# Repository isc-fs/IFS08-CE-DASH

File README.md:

# IFS08 - CE_DASH

Embedded firmware for the **Dashboard (DASH)** of the IFS08, developed on STM32.

---

## Getting started

1. Create a GitHub account if you don't have one yet.
2. Download and install [GitHub Desktop](https://desktop.github.com/) (beginner) or [Git CLI](https://git-scm.com/book/en/v2/Getting-Started-Installing-Git) (advanced).

   - If this is your first time using GitHub Desktop, make sure to read the [User Manual](https://help.github.com/desktop/guides/).
   - If this is your first time using Git, start with a tutorial. There are many available online:
     - [Git Tutorial](https://git-scm.com/docs/gittutorial)
     - [Atlassian Git Tutorial](https://www.atlassian.com/git/tutorials/)
   - Keep a copy of [GitHub's Git Cheat Sheet](https://services.github.com/kit/downloads/github-git-cheat-sheet.pdf) handy as a reference.

3. Clone this repository to your machine:
   - SSH: `git@github.com:isc-fs/IFS08-CE-DASH.git`
   - HTTPS: `https://github.com/isc-fs/IFS08-CE-DASH.git`

---

## How we work with this repository

### Main branches

The repository has two permanent branches:

**`main`** is the production branch. It contains only validated code that can be flashed onto the car. Never work directly on it.

**`dev`** is the development branch. It is the integration point where everyone's work comes together. Never work directly on it either — all changes arrive through a feature branch.

```
main  ──────────────────●──────────────────────●──▶  (validated releases only)
                        ↑                      ↑
dev   ──────●───●───●───●───●───●───●───●───●──●──▶  (continuous integration)
            ↑   ↑       ↑   ↑   ↑       ↑   ↑
          feat/1 fix/1 feat/2 fix/2   feat/3 fix/3
```

### Feature branches

All work — whether a new feature or a bug fix — is done on a **feature branch** created from `dev`. When the work is ready, a Pull Request is opened toward `dev`, reviewed, merged, and the branch is deleted.

There are two branch types, each with its own independent numeric counter. Every branch name carries a short kebab-case title after the number so its purpose is visible at a glance:

```
feat/<n>-<short-title>   →  new functionality  (feat/1-frame-layout, feat/2-isotp, ...)
fix/<n>-<short-title>    →  bug fix            (fix/1-wrp-race,      fix/2-crc-pad,  ...)
```

The short title should be 2–4 lowercase words joined by dashes. The `feat` and `fix` counters are independent: `feat/2-…` and `fix/2-…` can exist at the same time with no conflict.

### Tracking branch history

Feature branches are deleted after merging to keep the repository clean. The history of each branch is preserved in **GitHub Issues**.

Every branch has one associated issue. The issue carries a **label** (`feat` or `fix`) and its title includes the full branch name, for example: `[feat/3-can-broadcast] Add CAN broadcast for mission state`. When the branch is merged and deleted, the issue is closed — becoming a permanent record of all the work done.

To see which branches are currently active: filter issues by label and status `open`.
To browse the full history: filter by label and status `closed`.
The number for the next branch of each type is the last closed issue of that type plus one.

> Example: if the last closed issue with label `feat` is `[feat/4-…] ...`, the next feature branch will be `feat/5-<your-title>`.

---

## Automation

The repository includes a GitHub Actions workflow that manages tracking issues automatically. No setup is required — it works for every developer as soon as they create a branch.

### Automatic issue creation

When a `feat/*` or `fix/*` branch is pushed to GitHub, the workflow automatically opens an issue with:

- A title that mirrors the branch name — `[feat/N-short-title]` or `[fix/N-short-title]`
- The correct label (`feat` or `fix`)
- A template with sections for describing the work and adding notes
- The name of the developer who created the branch

### Wrong number warning

If the branch number is not the next expected one (either too low or too high), the issue will display a warning indicating the correct number and asking the developer to delete and recreate the branch with the right name.

### Auto-fill description from first commit

When the developer makes their first commit and pushes it, the workflow automatically updates the *"What does this branch do?"* section of the issue with that commit message.

- If the developer manually edits the issue before pushing their first commit, the workflow will not overwrite the description.
- The description is only updated once — subsequent commits do not modify the issue.

---

## Step-by-step workflow

### 1. Create the branch

```bash
# Make sure you are on an up-to-date dev
git checkout dev
git pull origin dev

# Create your branch using the next available number for its type
# (last closed issue of that type + 1) plus a short kebab-case title
git checkout -b feat/5-frame-layout    # or fix/3-wrp-race, etc.
```

> To find the right number: go to **Issues → filter by label `feat` or `fix` → sort by newest** and read the last number.

### 2. Push the branch

```bash
git push origin feat/5-frame-layout
```

The tracking issue will be opened automatically on GitHub within seconds.

### 3. Work and commit

```bash
# Make your changes and commit with a clear, descriptive message
git add .
git commit -m "short description of what this commit does"

# Push the changes
git push origin feat/5-frame-layout
```

The message of your **first commit** will be used to automatically fill in the issue description.

### 4. Open a Pull Request

When the work is ready, open a Pull Request on GitHub from your branch toward `dev`. In the PR description write `Closes #<issue-number>` so the issue closes automatically when the PR is merged.

Before requesting a review, check that:
- The code compiles with no errors or warnings
- You have tested the change on the bench if applicable
- The PR targets `dev`, not `main`

### 5. Review and merge

Another team member will review the PR. Once approved, it is merged into `dev` and the branch is deleted. The issue will be closed as a permanent record.

### 6. Merging into main

When `dev` holds a set of validated changes that are ready for the car, a responsible team member opens a Pull Request from `dev` into `main`. This only happens after full firmware validation (HIL/bench).

---

*ISC Racing Team — IFS08 Car Electronics*

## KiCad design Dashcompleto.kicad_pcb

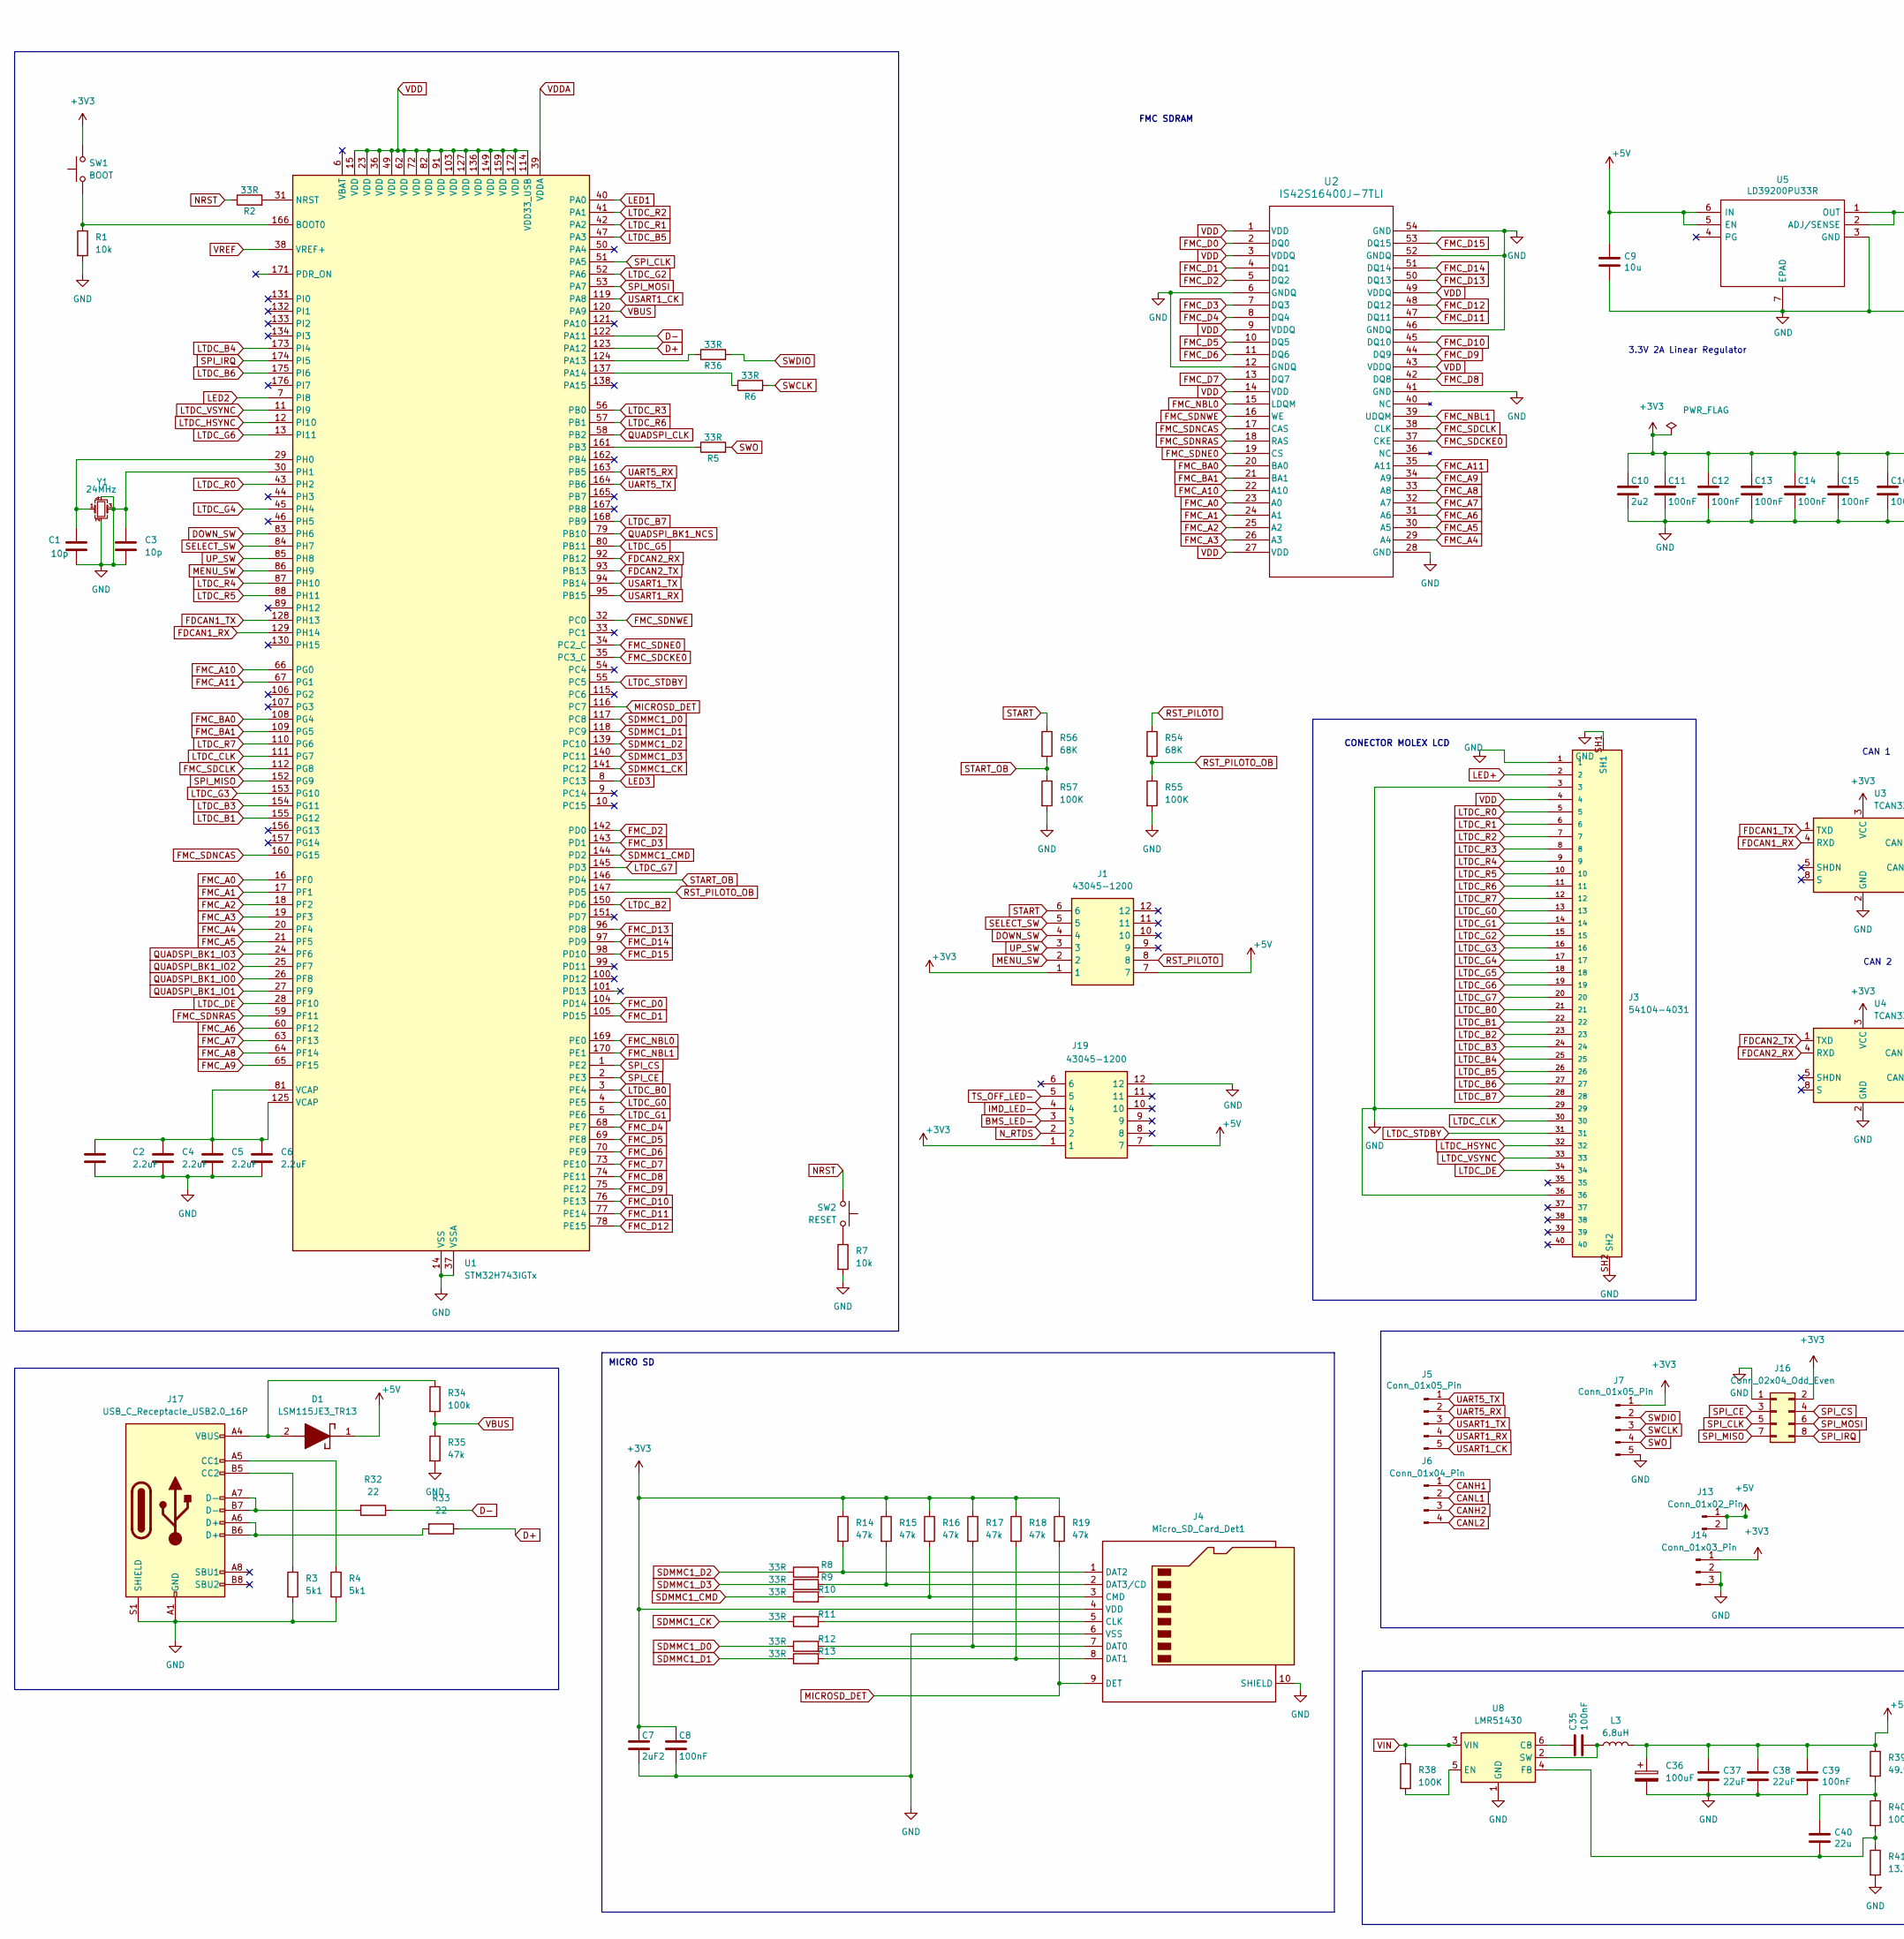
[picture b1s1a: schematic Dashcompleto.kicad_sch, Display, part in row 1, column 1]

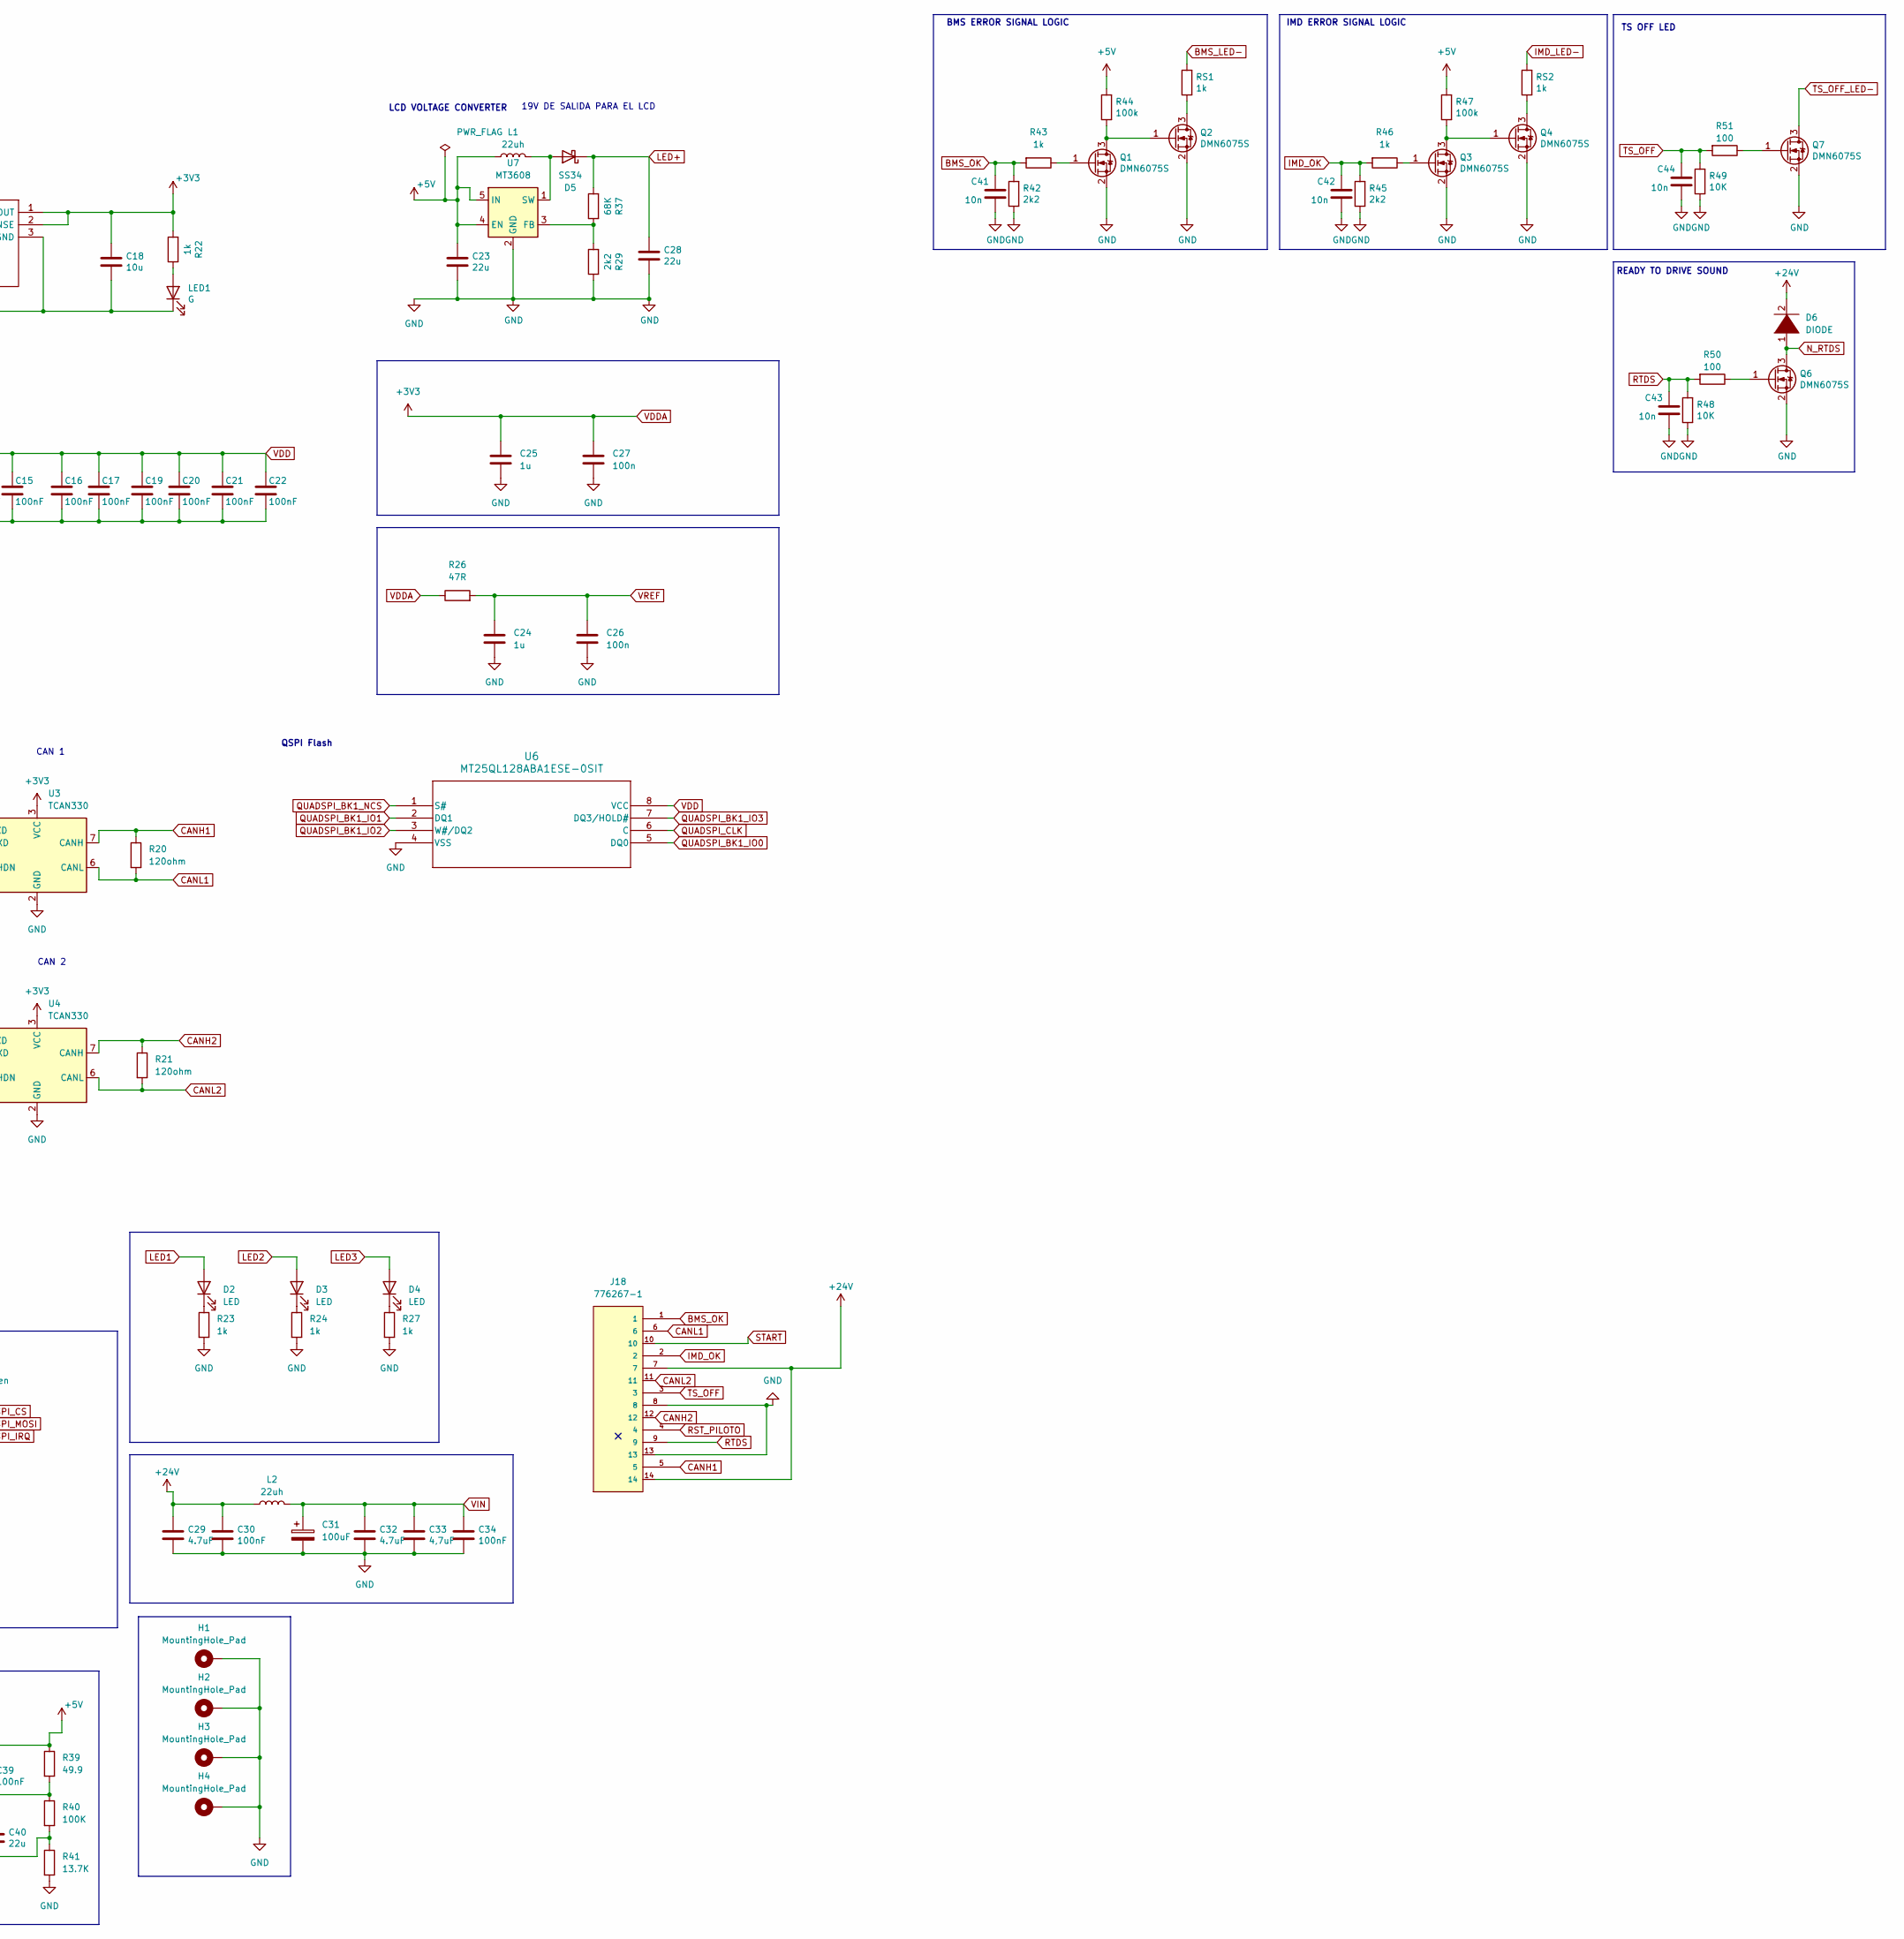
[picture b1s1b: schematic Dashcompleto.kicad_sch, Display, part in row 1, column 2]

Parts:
C1, C3: 10p; C_0805_2012Metric_Pad1.18x1.45mm_HandSolder
C2, C4, C5, C6: 2.2uF; C_0805_2012Metric_Pad1.18x1.45mm_HandSolder
C7: 2uF2; C_0805_2012Metric_Pad1.18x1.45mm_HandSolder
C8, C11, C12, C13, C14, C15, C16, C17, C19, C20, C21, C22, C30, C34, C35, C39: 100nF; C_0805_2012Metric_Pad1.18x1.45mm_HandSolder
C9, C18: 10u; C_0805_2012Metric_Pad1.18x1.45mm_HandSolder
C10: 2u2; C_0805_2012Metric_Pad1.18x1.45mm_HandSolder
C23, C28, C40: 22u; C_0805_2012Metric_Pad1.18x1.45mm_HandSolder
C24, C25: 1u; C_0805_2012Metric_Pad1.18x1.45mm_HandSolder
C26, C27: 100n; C_0805_2012Metric_Pad1.18x1.45mm_HandSolder
C29, C32: 4.7uF; C_0805_2012Metric_Pad1.18x1.45mm_HandSolder
C31, C36: 100uF; C_0805_2012Metric_Pad1.18x1.45mm_HandSolder
C33: 4,7uF; C_0805_2012Metric_Pad1.18x1.45mm_HandSolder
C37, C38: 22uF; C_0805_2012Metric_Pad1.18x1.45mm_HandSolder
C41, C42, C43, C44: 10n; C_1210_3225Metric
D1: LSM115JE3_TR13; DIOM5436X330N; Mouser Part Number 494-LSM115JE3/TR13
D2, D3, D4: LED; LED_0805_2012Metric_Pad1.15x1.40mm_HandSolder
D5: SS34; D_SMA
D6: DIODE; D_0805_2012Metric_Pad1.15x1.40mm_HandSolder
H1, H2, H3, H4: MountingHole_Pad; MountingHole_3.2mm_M3_ISO14580_Pad_TopBottom
J1, J19: 43045-1200; Molex_Micro-Fit_3.0_43045-1200_2x06_P3.00mm_Horizontal; Manufacturer_Part_Number 43045-1200
J3: 54104-4031; MOLEX_54104-4031; PARTREV A
J4: Micro_SD_Card_Det1; microSD_HC_Molex_104031-0811
J5, J7: Conn_01x05_Pin; PinHeader_1x05_P2.54mm_Vertical
J6: Conn_01x04_Pin; PinHeader_1x04_P2.54mm_Vertical
J13: Conn_01x02_Pin; PinHeader_1x02_P2.54mm_Vertical
J14: Conn_01x03_Pin; PinHeader_1x03_P2.54mm_Vertical
J16: Conn_02x04_Odd_Even; PinHeader_2x04_P2.54mm_Vertical
J17: USB_C_Receptacle_USB2.0_16P; USB_C_Receptacle_GCT_USB4085
J18: 776267-1; PARTREV B7
L1, L2: 22uh; L_Bourns_SRP7028A_7.3x6.6mm
L3: 6.8uH; L_Bourns_SRP7028A_7.3x6.6mm
LED1: G; LED_0805_2012Metric
Q1, Q2, Q3, Q4, Q6, Q7: DMN6075S; SOT-23
R1, R7: 10k; R_0805_2012Metric_Pad1.20x1.40mm_HandSolder
R2, R5, R6, R8, R9, R10, R11, R12, R13, R36: 33R; R_0805_2012Metric_Pad1.20x1.40mm_HandSolder
R3, R4: 5k1; R_0805_2012Metric_Pad1.20x1.40mm_HandSolder
R14, R15, R16, R17, R18, R19, R35: 47k; R_0805_2012Metric_Pad1.20x1.40mm_HandSolder
R20, R21: 120ohm; R_0805_2012Metric_Pad1.20x1.40mm_HandSolder
R22, R23, R24, R27: 1k; R_0805_2012Metric_Pad1.20x1.40mm_HandSolder
R26: 47R; R_0805_2012Metric_Pad1.20x1.40mm_HandSolder
R29: 2k2; R_0805_2012Metric_Pad1.20x1.40mm_HandSolder
R32, R33: 22; R_0603_1608Metric_Pad0.98x0.95mm_HandSolder
R34: 100k; R_0805_2012Metric_Pad1.20x1.40mm_HandSolder
R37, R54, R56: 68K; R_0805_2012Metric_Pad1.20x1.40mm_HandSolder
R38, R40, R55, R57: 100K; R_0805_2012Metric_Pad1.20x1.40mm_HandSolder
R39: 49.9; R_0805_2012Metric_Pad1.20x1.40mm_HandSolder
R41: 13.7K; R_0805_2012Metric_Pad1.20x1.40mm_HandSolder
R42, R45: 2k2; R_1206_3216Metric
R43, R46: 1k; R_1206_3216Metric
R44, R47: 100k; R_1206_3216Metric
R48, R49: 10K; R_1206_3216Metric
R50, R51: 100; R_1206_3216Metric
RS1, RS2: 1k; R_1206_3216Metric
SW1: BOOT; SW_SPST_B3U-1000P-B
SW2: RESET; SW_SPST_B3U-1000P-B
U1: STM32H743IGTx; LQFP-176_24x24mm_P0.5mm
U2: IS42S16400J-7TLI; 54L_TSOP-2_400_ISI
U3, U4: TCAN330; SOIC-8_3.9x4.9mm_P1.27mm
U5: LD39200PU33R; SON95P300X300X100-7N-D; Manufacturer_Part_Number LD39200PU33R; Mouser Part Number 511-LD39200PU33R
U6: MT25QL128ABA1ESE-0SIT; SOP2_8PIN_208MIL_MRN
U7: MT3608; SOT-23-6
U8: LMR51430; SOT-23-6
Y1: 24MHz; Crystal_SMD_2520-4Pin_2.5x2.0mm

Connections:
+5V: C9.1, C23.1, C36.1, C37.1, C38.1, C39.1, D1.1 (K), J1.7, J13.1, J13.2, J19.7, L1.1, L3.2, R39.1, R44.2, R47.2, U5.5 (EN), U5.6 (IN), U7.4 (EN), U7.5 (IN)
+24V: C29.1, C30.1, D6.2 (A), J18.7, J18.14, L2.1
BMS_LED-: J19.3, RS1.2
BMS_OK: C41.1, J18.1, R42.2, R43.2
CANH1: J6.1, J18.5, R20.1, U3.7 (CANH)
CANH2: J6.3, J18.12, R21.1, U4.7 (CANH)
CANL1: J6.2, J18.6, R20.2, U3.6 (CANL)
CANL2: J6.4, J18.11, R21.2, U4.6 (CANL)
D+: R33.1, U1.123 (PA12)
D-: R32.1, U1.122 (PA11)
DOWN_SW: J1.4, U1.83 (PH6)
FDCAN1_RX: U1.129 (PH14), U3.4 (RXD)
FDCAN1_TX: U1.128 (PH13), U3.1 (TXD)
FDCAN2_RX: U1.92 (PB12), U4.4 (RXD)
FDCAN2_TX: U1.93 (PB13), U4.1 (TXD)
FMC_A0: U1.16 (PF0), U2.23 (A0)
FMC_A1: U1.17 (PF1), U2.24 (A1)
FMC_A2: U1.18 (PF2), U2.25 (A2)
FMC_A3: U1.19 (PF3), U2.26 (A3)
FMC_A4: U1.20 (PF4), U2.29 (A4)
FMC_A5: U1.21 (PF5), U2.30 (A5)
FMC_A6: U1.60 (PF12), U2.31 (A6)
FMC_A7: U1.63 (PF13), U2.32 (A7)
FMC_A8: U1.64 (PF14), U2.33 (A8)
FMC_A9: U1.65 (PF15), U2.34 (A9)
FMC_A10: U1.66 (PG0), U2.22 (A10)
FMC_A11: U1.67 (PG1), U2.35 (A11)
FMC_BA0: U1.108 (PG4), U2.20 (BA0)
FMC_BA1: U1.109 (PG5), U2.21 (BA1)
FMC_D0: U1.104 (PD14), U2.2 (DQ0)
FMC_D1: U1.105 (PD15), U2.4 (DQ1)
FMC_D2: U1.142 (PD0), U2.5 (DQ2)
FMC_D3: U1.143 (PD1), U2.7 (DQ3)
FMC_D4: U1.68 (PE7), U2.8 (DQ4)
FMC_D5: U1.69 (PE8), U2.10 (DQ5)
FMC_D6: U1.70 (PE9), U2.11 (DQ6)
FMC_D7: U1.73 (PE10), U2.13 (DQ7)
FMC_D8: U1.74 (PE11), U2.42 (DQ8)
FMC_D9: U1.75 (PE12), U2.44 (DQ9)
FMC_D10: U1.76 (PE13), U2.45 (DQ10)
FMC_D11: U1.77 (PE14), U2.47 (DQ11)
FMC_D12: U1.78 (PE15), U2.48 (DQ12)
FMC_D13: U1.96 (PD8), U2.50 (DQ13)
FMC_D14: U1.97 (PD9), U2.51 (DQ14)
FMC_D15: U1.98 (PD10), U2.53 (DQ15)
FMC_NBL0: U1.169 (PE0), U2.15 (LDQM)
FMC_NBL1: U1.170 (PE1), U2.39 (UDQM)
FMC_SDCKE0: U1.35 (PC3_C), U2.37 (CKE)
FMC_SDCLK: U1.112 (PG8), U2.38 (CLK)
FMC_SDNCAS: U1.160 (PG15), U2.17 (CAS)
FMC_SDNE0: U1.34 (PC2_C), U2.19 (CS)
FMC_SDNRAS: U1.59 (PF11), U2.18 (RAS)
FMC_SDNWE: U1.32 (PC0), U2.16 (WE)
GND: C1.2, C2.2, C3.1, C3.2, C4.2, C5.2, C6.2, C7.2, C8.2, C9.2, C10.2, C11.2, C12.2, C13.2, C14.2, C15.2, C16.2, C17.2, C18.2, C19.2, C20.2, C21.2, C22.2, C23.2, C24.1, C25.1, C26.1, C27.1, C28.2, C29.2, C30.2, C31.2, C32.2, C33.2, C34.2, C36.2, C37.2, C38.2, C39.2, C41.2, C42.2, C43.2, C44.2, H1.1, H2.1, H3.1, H4.1, J3.1, J3.3, J3.29, J3.36, J3.SH1, J3.SH2, J4.6 (VSS), J4.10 (SHIELD), J7.5, J14.2, J14.3, J16.1, J17.A1 (GND), J17.A12 (GND), J17.B1 (GND), J17.B12 (GND), J17.S1 (SHIELD), J18.8, J18.13, J19.12, LED1.1 (K), Q1.2 (S), Q2.2 (S), Q3.2 (S), Q4.2 (S), Q6.2 (S), Q7.2 (S), R1.2, R3.2, R4.2, R7.2, R23.2, R24.2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
IMD_LED-: J19.4, RS2.2
IMD_OK: C42.1, J18.2, R45.2, R46.2
LED1: D2.2 (A), U1.40 (PA0)
LED2: D3.2 (A), U1.7 (PI8)
LED3: D4.2 (A), U1.8 (PC13)
LED+: C28.1, D5.1 (K), J3.2, R37.2
LTDC_B0: J3.21, U1.3 (PE4)
LTDC_B1: J3.22, U1.155 (PG12)
LTDC_B2: J3.23, U1.150 (PD6)
LTDC_B3: J3.24, U1.154 (PG11)
LTDC_B4: J3.25, U1.173 (PI4)
LTDC_B5: J3.26, U1.47 (PA3)
LTDC_B6: J3.27, U1.175 (PI6)
LTDC_B7: J3.28, U1.168 (PB9)
LTDC_CLK: J3.30, U1.111 (PG7)
LTDC_DE: J3.34, U1.28 (PF10)
LTDC_G0: J3.13, U1.4 (PE5)
LTDC_G1: J3.14, U1.5 (PE6)
LTDC_G2: J3.15, U1.52 (PA6)
LTDC_G3: J3.16, U1.153 (PG10)
LTDC_G4: J3.17, U1.45 (PH4)
LTDC_G5: J3.18, U1.80 (PB11)
LTDC_G6: J3.19, U1.13 (PI11)
LTDC_G7: J3.20, U1.145 (PD3)
LTDC_HSYNC: J3.32, U1.12 (PI10)
LTDC_R0: J3.5, U1.43 (PH2)
LTDC_R1: J3.6, U1.42 (PA2)
LTDC_R2: J3.7, U1.41 (PA1)
LTDC_R3: J3.8, U1.56 (PB0)
LTDC_R4: J3.9, U1.87 (PH10)
LTDC_R5: J3.10, U1.88 (PH11)
LTDC_R6: J3.11, U1.57 (PB1)
LTDC_R7: J3.12, U1.110 (PG6)
LTDC_STDBY: J3.31, U1.55 (PC5)
LTDC_VSYNC: J3.33, U1.11 (PI9)
MENU_SW: J1.2, U1.86 (PH9)
MICROSD_DET: J4.9 (DET), R19.2, U1.116 (PC7)
NRST: R2.1, SW2.2
N_RTDS: D6.1 (K), J19.2, Q6.3 (D)
unnamed: C2.1, C4.1, C5.1, C6.1, U1.81 (VCAP), U1.125 (VCAP)
unnamed: C40.1, R39.2, R40.1
unnamed: D1.2 (A), J17.A4 (VBUS), J17.A9 (VBUS), J17.B4 (VBUS), J17.B9 (VBUS), R34.1
unnamed: D2.1 (K), R23.1
unnamed: D3.1 (K), R24.1
unnamed: D4.1 (K), R27.1
unnamed: D5.2 (A), L1.2, U7.1 (SW)
unnamed: J4.5 (CLK), R11.2
unnamed: J4.3 (CMD), R10.2, R16.2
unnamed: J4.7 (DAT0), R12.2, R17.2
unnamed: J4.8 (DAT1), R13.2, R18.2
unnamed: J4.1 (DAT2), R8.2, R14.2
unnamed: J4.2 (DAT3/CD), R9.2, R15.2
unnamed: J17.A5 (CC1), R4.1
unnamed: J17.B5 (CC2), R3.1
unnamed: J17.A6 (D+), J17.B6 (D+), R33.2
unnamed: J17.A7 (D-), J17.B7 (D-), R32.2
unnamed: LED1.2 (A), R22.1
unnamed: Q1.3 (D), Q2.1 (G), R44.1
unnamed: Q1.1 (G), R43.1
unnamed: Q2.3 (D), RS1.1
unnamed: Q3.3 (D), Q4.1 (G), R47.1
unnamed: Q3.1 (G), R46.1
unnamed: Q4.3 (D), RS2.1
unnamed: Q6.1 (G), R50.1
unnamed: Q7.1 (G), R51.1
unnamed: R7.1, SW2.1
unnamed: R1.1, SW1.1, U1.166 (BOOT0)
unnamed: R2.2, U1.31 (NRST)
unnamed: R36.1, U1.124 (PA13)
unnamed: R6.1, U1.137 (PA14)
unnamed: R5.1, U1.161 (PB3)
unnamed: C1.1, U1.29 (PH0), Y1.1
unnamed: R29.2, R37.1, U7.3 (FB)
unnamed: C35.1, U8.6 (CB)
unnamed: R38.2, U8.5 (EN)
unnamed: C40.2, R40.2, R41.1, U8.4 (FB)
unnamed: C35.2, L3.1, U8.2 (SW)
QUADSPI_BK1_IO0: U1.26 (PF8), U6.5 (DQ0)
QUADSPI_BK1_IO1: U1.27 (PF9), U6.2 (DQ1)
QUADSPI_BK1_IO2: U1.25 (PF7), U6.3 (W#/DQ2)
QUADSPI_BK1_IO3: U1.24 (PF6), U6.7 (DQ3/HOLD#)
QUADSPI_BK1_NCS: U1.79 (PB10), U6.1 (S#)
QUADSPI_CLK: U1.58 (PB2), U6.6 (C)
RST_PILOTO: J1.8, J18.4, R54.1
RST_PILOTO_OB: R54.2, R55.1, U1.147 (PD5)
RTDS: C43.1, J18.9, R48.2, R50.2
SDMMC1_CK: R11.1, U1.141 (PC12)
SDMMC1_CMD: R10.1, U1.144 (PD2)
SDMMC1_D0: R12.1, U1.117 (PC8)
SDMMC1_D1: R13.1, U1.118 (PC9)
SDMMC1_D2: R8.1, U1.139 (PC10)
SDMMC1_D3: R9.1, U1.140 (PC11)
SELECT_SW: J1.5, U1.84 (PH7)
SPI_CE: J16.3, U1.2 (PE3)
SPI_CLK: J16.5, U1.51 (PA5)
SPI_CS: J16.4, U1.1 (PE2)
SPI_IRQ: J16.8, U1.174 (PI5)
SPI_MISO: J16.7, U1.152 (PG9)
SPI_MOSI: J16.6, U1.53 (PA7)
START: J1.6, J18.10, R56.1
START_OB: R56.2, R57.1, U1.146 (PD4)
SWCLK: J7.3, R6.2
SWDIO: J7.2, R36.2
SWO: J7.4, R5.2
TS_OFF: C44.1, J18.3, R49.2, R51.2
TS_OFF_LED-: J19.5, Q7.3 (D)
UART5_RX: J5.2, U1.163 (PB5)
UART5_TX: J5.1, U1.164 (PB6)
UP_SW: J1.3, U1.85 (PH8)
USART1_CK: J5.5, U1.119 (PA8)
USART1_RX: J5.4, U1.95 (PB15)
USART1_TX: J5.3, U1.94 (PB14)
VBUS: R34.2, R35.1, U1.120 (PA9)
VDD: C7.1, C8.1, C10.1, C11.1, C12.1, C13.1, C14.1, C15.1, C16.1, C17.1, C18.1, C19.1, C20.1, C21.1, C22.1, C25.2, C27.2, J1.1, J3.4, J4.4 (VDD), J7.1, J14.1, J16.2, J19.1, R14.1, R15.1, R16.1, R17.1, R18.1, R19.1, R22.2, R26.1, SW1.2, U1.15 (VDD), U1.23 (VDD), U1.36 (VDD), U1.39 (VDDA), U1.49 (VDD), U1.62 (VDD), U1.72 (VDD), U1.82 (VDD), U1.91 (VDD), U1.103 (VDD), U1.114 (VDD33_USB), U1.127 (VDD), U1.136 (VDD), U1.149 (VDD), U1.159 (VDD), U1.172 (VDD), U2.1 (VDD), U2.3 (VDDQ), U2.9 (VDDQ), U2.14 (VDD), U2.27 (VDD), U2.43 (VDDQ), U2.49 (VDDQ), U3.3 (VCC), U4.3 (VCC), U5.1 (OUT), U5.2 (ADJ/SENSE), U6.8 (VCC)
VIN: C31.1, C32.1, C33.1, C34.1, L2.2, R38.1, U8.3 (VIN)
VREF: C24.2, C26.2, R26.2, U1.38 (VREF+)

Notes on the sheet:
QSPI Flash
READY TO DRIVE SOUND
CONECTOR MOLEX LCD
MICRO SD
BMS ERROR SIGNAL LOGIC
LCD VOLTAGE CONVERTER
3.3V 2A Linear Regulator
19V DE SALIDA PARA EL LCD
CAN 2
FMC SDRAM
CAN 1
IMD ERROR SIGNAL LOGIC
TS OFF LED

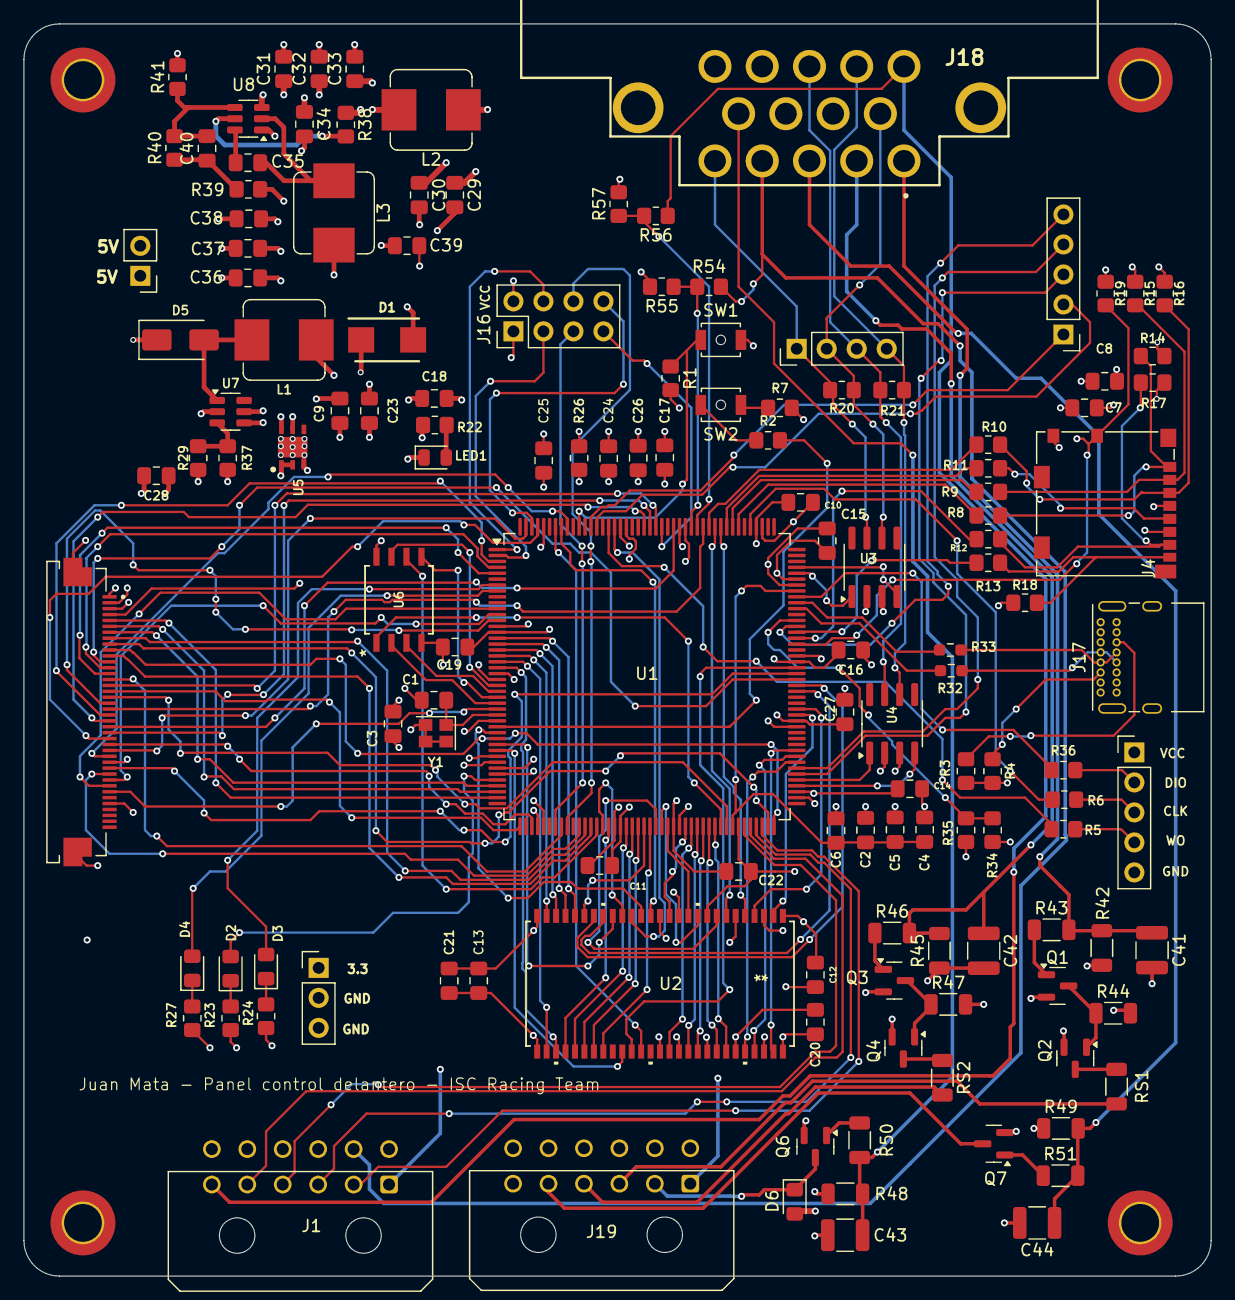
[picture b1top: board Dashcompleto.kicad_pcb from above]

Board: 4 copper layers, 100.5 x 106.0 mm, 140 parts (0 on the bottom side), 170 nets.

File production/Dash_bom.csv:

Designator,Footprint,Quantity,Value,LCSC Part #
"C1, C3",0805,2,10p,
C10,0805,1,2u2,
"C11, C12, C13, C14, C15, C16, C17, C19, C20, C21, C22, C30, C34, C35, C39, C8",0805,16,100nF,
"C18, C9",0805,2,10u,
"C2, C4, C5, C6",0805,4,2.2uF,
"C23, C28, C40",0805,3,22u,
"C24, C25",0805,2,1u,
"C26, C27",0805,2,100n,
"C29, C32",0805,2,4.7uF,
"C31, C36",0805,2,100uF,
C33,0805,1,"4,7uF",
"C37, C38",0805,2,22uF,
"C41, C42, C43, C44",1210,4,10n,
C7,0805,1,2uF2,
D1,DIOM5436X330N,1,LSM115JE3_TR13,
"D2, D3, D4",0805,3,LED,
D5,D_SMA,1,SS34,
D6,0805,1,DIODE,
"J1, J19",Molex_Micro-Fit_3.0_43045-1200_2x06_P3.00mm_Horizontal,2,43045-1200,
J13,PinHeader_1x02_P2.54mm_Vertical,1,Conn_01x02_Pin,
J14,PinHeader_1x03_P2.54mm_Vertical,1,Conn_01x03_Pin,
J16,PinHeader_2x04_P2.54mm_Vertical,1,Conn_02x04_Odd_Even,
J17,USB_C_Receptacle_GCT_USB4085,1,USB_C_Receptacle_USB2.0_16P,
J18,776267-1,1,776267-1,
J3,MOLEX_54104-4031,1,54104-4031,
J4,microSD_HC_Molex_104031-0811,1,Micro_SD_Card_Det1,
"J5, J7",PinHeader_1x05_P2.54mm_Vertical,2,Conn_01x05_Pin,
J6,PinHeader_1x04_P2.54mm_Vertical,1,Conn_01x04_Pin,
"L1, L2",L_Bourns_SRP7028A_7.3x6.6mm,2,22uh,
L3,L_Bourns_SRP7028A_7.3x6.6mm,1,6.8uH,
LED1,0805,1,G,
"Q1, Q2, Q3, Q4, Q6, Q7",SOT-23,6,DMN6075S,
"R1, R7",0805,2,10k,
"R10, R11, R12, R13, R2, R36, R5, R6, R8, R9",0805,10,33R,
"R14, R15, R16, R17, R18, R19, R35",0805,7,47k,
"R20, R21",0805,2,120ohm,
"R22, R23, R24, R27",0805,4,1k,
R26,0805,1,47R,
R29,0805,1,2k2,
"R3, R4",0805,2,5k1,
"R32, R33",0603,2,22,
"R34, R38, R40, R55, R57",0805,5,100k,
"R37, R54, R56",0805,3,68K,
R39,0805,1,49.9,
R41,0805,1,13.7K,
"R42, R45",1206,2,2k2,
"R43, R46, RS1, RS2",1206,4,1k,
"R44, R47",1206,2,100k,
"R48, R49",1206,2,10K,
"R50, R51",1206,2,100,
SW1,SW_SPST_B3U-1000P-B,1,BOOT,
SW2,SW_SPST_B3U-1000P-B,1,RESET,
U1,LQFP-176_24x24mm_P0.5mm,1,STM32H743IGTx,
U2,54L_TSOP-2_400_ISI,1,IS42S16400J-7TLI,
"U3, U4",SOIC-8_3.9x4.9mm_P1.27mm,2,TCAN330,
U5,SON95P300X300X100-7N-D,1,LD39200PU33R,
U6,SOP2_8PIN_208MIL_MRN,1,MT25QL128ABA1ESE-0SIT,
U7,SOT-23-6,1,MT3608,
U8,SOT-23-6,1,LMR51430,
Y1,Crystal_SMD_2520-4Pin_2.5x2.0mm,1,24MHz,

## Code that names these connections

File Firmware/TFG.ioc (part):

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Mcu.Name=STM32H743IGTx
Mcu.Package=LQFP176
Mcu.UserName=STM32H743IGTx
PA0.GPIOParameters=GPIO_Label
PA0.GPIO_Label=LED1
PA0.Signal=GPIO_Output
PA1.Mode=RGB888
PA1.Signal=LTDC_R2
PA11.Mode=Device_Only
PA11.Signal=USB_OTG_FS_DM
PA12.Mode=Device_Only
PA12.Signal=USB_OTG_FS_DP
PA13\ (JTMS/SWDIO).Mode=Serial_Wire
PA13\ (JTMS/SWDIO).Signal=DEBUG_JTMS-SWDIO
PA14\ (JTCK/SWCLK).Mode=Serial_Wire
PA14\ (JTCK/SWCLK).Signal=DEBUG_JTCK-SWCLK
PA2.Mode=RGB888
PA2.Signal=LTDC_R1
PA3.Mode=RGB888
PA3.Signal=LTDC_B5
PA5.Mode=Full_Duplex_Master
PA5.Signal=SPI1_SCK
PA6.Mode=RGB888
PA6.Signal=LTDC_G2
PA7.Mode=Full_Duplex_Master
PA7.Signal=SPI1_MOSI
PA8.Mode=Synchronous
PA8.Signal=USART1_CK
PA9.Mode=Activate_VBUS
PA9.Signal=USB_OTG_FS_VBUS
PB0.Mode=RGB888
PB0.Signal=LTDC_R3
PB1.Mode=RGB888
PB1.Signal=LTDC_R6
PB10.Mode=Single Bank 1
PB10.Signal=QUADSPI_BK1_NCS
PB11.Mode=RGB888
PB11.Signal=LTDC_G5
PB12.Mode=FDCAN_Activate
PB12.Signal=FDCAN2_RX
PB13.Mode=FDCAN_Activate
PB13.Signal=FDCAN2_TX
PB14.Mode=Synchronous
PB14.Signal=USART1_TX
PB15.Mode=Synchronous
PB15.Signal=USART1_RX
PB2.Mode=Single Bank 1
PB2.Signal=QUADSPI_CLK
PB5.Mode=Asynchronous
PB5.Signal=UART5_RX
PB6.Mode=Asynchronous
PB6.Signal=UART5_TX
PB9.Mode=RGB888
PB9.Signal=LTDC_B7
PC0.Signal=FMC_SDNWE
PC10.Mode=SD_4_bits_Wide_bus
PC10.Signal=SDMMC1_D2
PC11.Mode=SD_4_bits_Wide_bus
PC11.Signal=SDMMC1_D3
PC12.Mode=SD_4_bits_Wide_bus
PC12.Signal=SDMMC1_CK
PC13.GPIOParameters=GPIO_Label
PC13.GPIO_Label=LED3
PC13.Signal=GPIO_Output
PC2_C.Mode=SdramChipSelect1_1
PC2_C.Signal=FMC_SDNE0
PC3_C.Mode=SdramChipSelect1_1
PC3_C.Signal=FMC_SDCKE0
PC5.GPIOParameters=GPIO_Label
PC5.GPIO_Label=LTDC_STDBY
PC5.Signal=GPIO_Output
PC7.GPIOParameters=GPIO_Label
PC7.GPIO_Label=MICROSD_DET
PC7.Signal=GPIO_Input
PC8.Mode=SD_4_bits_Wide_bus
PC8.Signal=SDMMC1_D0
PC9.Mode=SD_4_bits_Wide_bus
PC9.Signal=SDMMC1_D1
PD0.Signal=FMC_D2_DA2
PD1.Signal=FMC_D3_DA3
PD10.Signal=FMC_D15_DA15
PD14.Signal=FMC_D0_DA0
PD15.Signal=FMC_D1_DA1
PD2.Mode=SD_4_bits_Wide_bus
PD2.Signal=SDMMC1_CMD
PD3.Mode=RGB888
PD3.Signal=LTDC_G7
PD6.Mode=RGB888
PD6.Signal=LTDC_B2
PD8.Signal=FMC_D13_DA13
PD9.Signal=FMC_D14_DA14
PE0.Signal=FMC_NBL0
PE1.Signal=FMC_NBL1
PE10.Signal=FMC_D7_DA7
PE11.Signal=FMC_D8_DA8
PE12.Signal=FMC_D9_DA9
PE13.Signal=FMC_D10_DA10
PE14.Signal=FMC_D11_DA11
PE15.Signal=FMC_D12_DA12
PE2.GPIOParameters=GPIO_Label
PE2.GPIO_Label=SPI_CS
PE2.Signal=GPIO_Output
PE3.GPIOParameters=GPIO_Label
PE3.GPIO_Label=SPI_CE
PE3.Signal=GPIO_Output
PE4.Mode=RGB888
PE4.Signal=LTDC_B0
PE5.Mode=RGB888
PE5.Signal=LTDC_G0
PE6.Mode=RGB888
PE6.Signal=LTDC_G1
PE7.Signal=FMC_D4_DA4
PE8.Signal=FMC_D5_DA5
PE9.Signal=FMC_D6_DA6
PF0.Signal=FMC_A0
PF1.Signal=FMC_A1
PF10.Mode=RGB888
PF10.Signal=LTDC_DE
PF11.Signal=FMC_SDNRAS
PF12.Signal=FMC_A6
PF13.Signal=FMC_A7
PF14.Signal=FMC_A8
PF15.Signal=FMC_A9
PF2.Signal=FMC_A2
PF3.Signal=FMC_A3
PF4.Signal=FMC_A4
PF5.Signal=FMC_A5
PF6.Mode=Single Bank 1
PF6.Signal=QUADSPI_BK1_IO3
PF7.Mode=Single Bank 1
PF7.Signal=QUADSPI_BK1_IO2
PF8.Mode=Single Bank 1
PF8.Signal=QUADSPI_BK1_IO0
PF9.Mode=Single Bank 1
PF9.Signal=QUADSPI_BK1_IO1
PG0.Signal=FMC_A10
PG1.Signal=FMC_A11
PG10.Mode=RGB888
PG10.Signal=LTDC_G3
PG11.Mode=RGB888
PG11.Signal=LTDC_B3
PG12.Mode=RGB888
PG12.Signal=LTDC_B1
PG15.Signal=FMC_SDNCAS
PG4.Signal=FMC_A14_BA0
PG5.Signal=FMC_A15_BA1
PG6.Mode=RGB888
PG6.Signal=LTDC_R7
PG7.Mode=RGB888
PG7.Signal=LTDC_CLK
PG8.Signal=FMC_SDCLK
PG9.Mode=Full_Duplex_Master
PG9.Signal=SPI1_MISO
PH0-OSC_IN\ (PH0).Mode=HSE-External-Oscillator
PH0-OSC_IN\ (PH0).Signal=RCC_OSC_IN
PH1-OSC_OUT\ (PH1).Mode=HSE-External-Oscillator
PH1-OSC_OUT\ (PH1).Signal=RCC_OSC_OUT
PH10.Mode=RGB888
PH10.Signal=LTDC_R4
PH11.Mode=RGB888
PH11.Signal=LTDC_R5
PH13.Mode=FDCAN_Activate
PH13.Signal=FDCAN1_TX
PH14.Mode=FDCAN_Activate
PH14.Signal=FDCAN1_RX
PH2.Mode=RGB888
PH2.Signal=LTDC_R0
PH4.Mode=RGB888
PH4.Signal=LTDC_G4
PH6.GPIOParameters=GPIO_Label
PH6.GPIO_Label=DOWN_SW
PH6.Signal=GPIO_Input
PH7.GPIOParameters=GPIO_Label
PH7.GPIO_Label=SELECT_SW
PH7.Signal=GPIO_Input
PH8.GPIOParameters=GPIO_Label
PH8.GPIO_Label=UP_SW
PH8.Signal=GPIO_Input
PH9.GPIOParameters=GPIO_Label
PH9.GPIO_Label=MENU_SW
PH9.Signal=GPIO_Input
PI10.Mode=RGB888
PI10.Signal=LTDC_HSYNC
PI11.Mode=RGB888
PI11.Signal=LTDC_G6
PI4.Mode=RGB888
PI4.Signal=LTDC_B4
PI5.GPIOParameters=GPIO_Label
PI5.GPIO_Label=SPI_IRQ
PI5.Signal=GPIO_Output
PI6.Mode=RGB888
PI6.Signal=LTDC_B6
PI8.GPIOParameters=GPIO_Label
PI8.GPIO_Label=LED2
PI8.Signal=GPIO_Output
PI9.Mode=RGB888
PI9.Signal=LTDC_VSYNC
RCC.HSE_VALUE=24000000
RCC.SYSCLKFreq_VALUE=240000000
RCC.SYSCLKSource=RCC_SYSCLKSOURCE_PLLCLK
board=custom

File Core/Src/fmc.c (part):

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  __HAL_RCC_FMC_CLK_ENABLE();

  /** FMC GPIO Configuration
  PF0   ------> FMC_A0
  PF1   ------> FMC_A1
  PF2   ------> FMC_A2
  PF3   ------> FMC_A3
  PF4   ------> FMC_A4
  PF5   ------> FMC_A5
  PC0   ------> FMC_SDNWE
  PC2_C   ------> FMC_SDNE0
  PC3_C   ------> FMC_SDCKE0
  PF11   ------> FMC_SDNRAS
  PF12   ------> FMC_A6
  PF13   ------> FMC_A7
  PF14   ------> FMC_A8
  PF15   ------> FMC_A9
  PG0   ------> FMC_A10
  PG1   ------> FMC_A11
  PE7   ------> FMC_D4
  PE8   ------> FMC_D5
  PE9   ------> FMC_D6
  PE10   ------> FMC_D7
  PE11   ------> FMC_D8
  PE12   ------> FMC_D9
  PE13   ------> FMC_D10
  PE14   ------> FMC_D11
  PE15   ------> FMC_D12
  PD8   ------> FMC_D13
  PD9   ------> FMC_D14
  PD10   ------> FMC_D15
  PD14   ------> FMC_D0
  PD15   ------> FMC_D1
  PG4   ------> FMC_BA0
  PG5   ------> FMC_BA1
  PG8   ------> FMC_SDCLK
  PD0   ------> FMC_D2
  PD1   ------> FMC_D3
  PG15   ------> FMC_SDNCAS
  PE0   ------> FMC_NBL0
  PE1   ------> FMC_NBL1
  */
  /* GPIO_InitStruct */
  GPIO_InitStruct.Pin = GPIO_PIN_0|GPIO_PIN_1|GPIO_PIN_2|GPIO_PIN_3
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  __HAL_RCC_FMC_CLK_DISABLE();

  /** FMC GPIO Configuration
  PF0   ------> FMC_A0
  PF1   ------> FMC_A1
  PF2   ------> FMC_A2
  PF3   ------> FMC_A3
  PF4   ------> FMC_A4
  PF5   ------> FMC_A5
  PC0   ------> FMC_SDNWE
  PC2_C   ------> FMC_SDNE0
  PC3_C   ------> FMC_SDCKE0
  PF11   ------> FMC_SDNRAS
  PF12   ------> FMC_A6
  PF13   ------> FMC_A7
  PF14   ------> FMC_A8
  PF15   ------> FMC_A9
  PG0   ------> FMC_A10
  PG1   ------> FMC_A11
  PE7   ------> FMC_D4
  PE8   ------> FMC_D5
  PE9   ------> FMC_D6
  PE10   ------> FMC_D7
  PE11   ------> FMC_D8
  PE12   ------> FMC_D9
  PE13   ------> FMC_D10
  PE14   ------> FMC_D11
  PE15   ------> FMC_D12
  PD8   ------> FMC_D13
  PD9   ------> FMC_D14
  PD10   ------> FMC_D15
  PD14   ------> FMC_D0
  PD15   ------> FMC_D1
  PG4   ------> FMC_BA0
  PG5   ------> FMC_BA1
  PG8   ------> FMC_SDCLK
  PD0   ------> FMC_D2
  PD1   ------> FMC_D3
  PG15   ------> FMC_SDNCAS
  PE0   ------> FMC_NBL0
  PE1   ------> FMC_NBL1
  */

  HAL_GPIO_DeInit(GPIOF, GPIO_PIN_0|GPIO_PIN_1|GPIO_PIN_2|GPIO_PIN_3
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

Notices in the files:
Core/Src/fmc.c:
Copyright (c) 2026 STMicroelectronics.
All rights reserved.
This software is licensed under terms that can be found in the LICENSE file
